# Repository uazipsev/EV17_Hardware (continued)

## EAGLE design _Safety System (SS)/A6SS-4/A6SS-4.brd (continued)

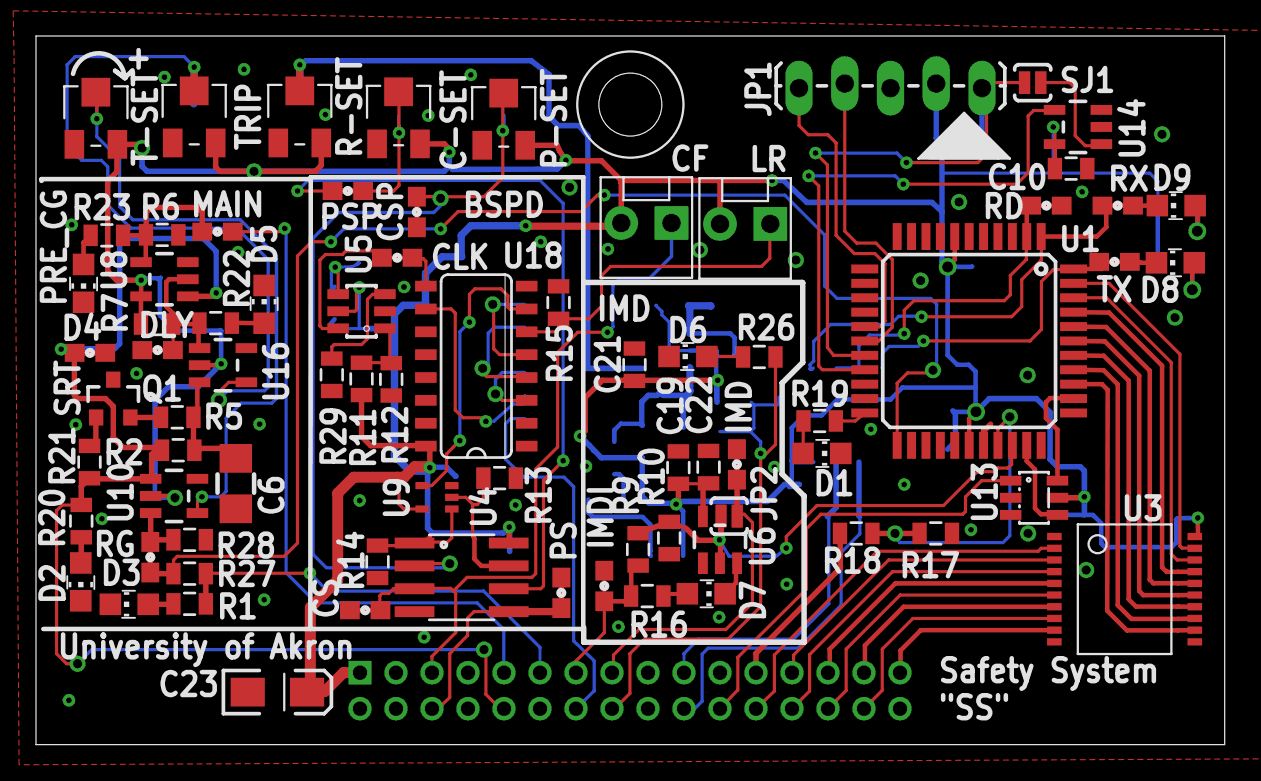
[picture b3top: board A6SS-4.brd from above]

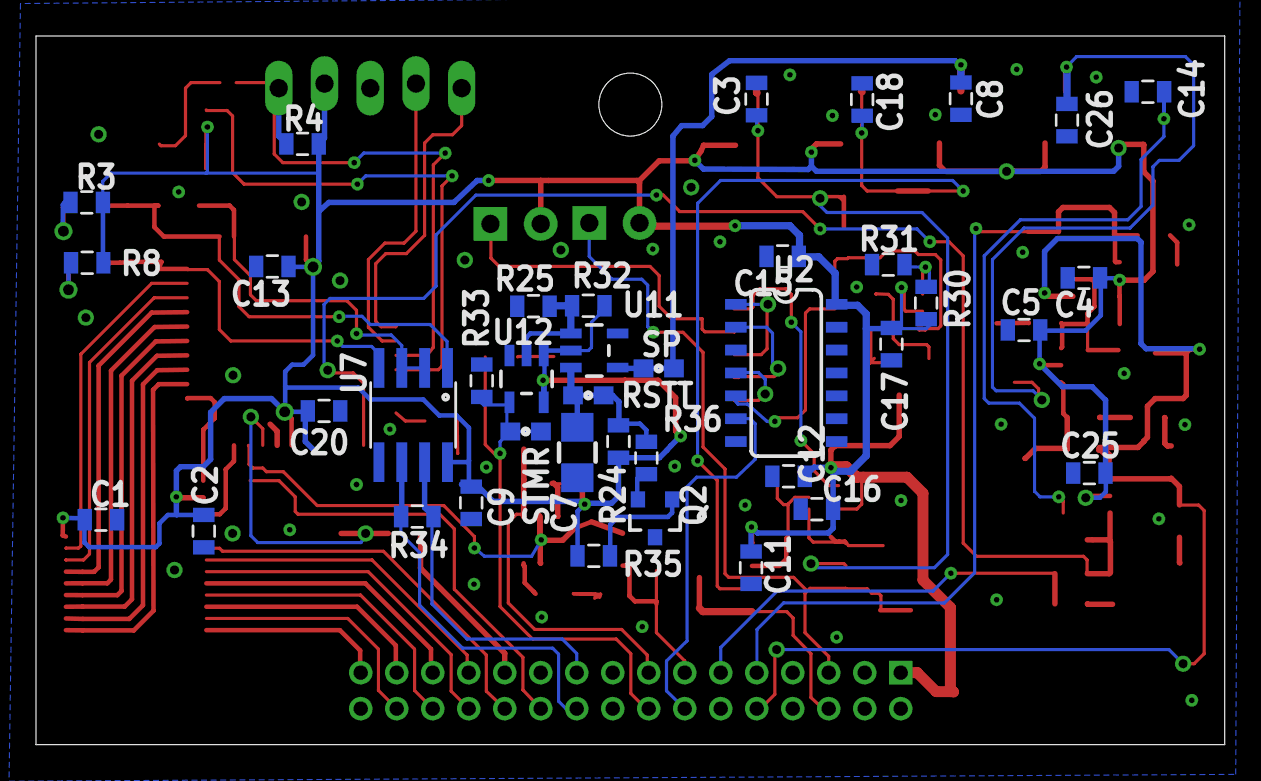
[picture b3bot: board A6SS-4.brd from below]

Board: 2 copper layers, 66.0 x 39.4 mm, 117 parts (39 on the bottom side), 79 nets.

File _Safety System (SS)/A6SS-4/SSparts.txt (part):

Partlist

Exported from A6SS-4.brd at 4/22/2016 5:32 PM

EAGLE Version 7.5.0 Copyright (c) 1988-2015 CadSoft

Assembly variant: 

Part     Value             Package            Library             Position (mil)        Orientation

C1       0.1UF             0805               FSAE Electric       (2457 491)            MR0
C2       0.1UF             0805               FSAE Electric       (2232 466)            MR270
C3       1UF               0805               FSAE Electric       (1023 1352)           MR270
C4       0.1UF             0805               FSAE Electric       (307 1020)            MR180
C5       0.1UF             0805               FSAE Electric       (438 906)             MR180
C6       100UF             1206               FSAE Electric       (436 570)             R270
C7       100UF             1206               FSAE Electric       (1342 689)            MR270
C8       1UF               0805               FSAE Electric       (576 1356)            MR270
C9       0.1UF             0805               FSAE Electric       (1671 530)            MR270
C10      0.1UF             0805               FSAE Electric       (2263 1259)           R0
C11      0.1UF             0805               FSAE Electric       (1035 386)            MR270
C12      0.1UF             0805               FSAE Electric       (891 514)             MR180
C13      0.1UF             0805               FSAE Electric       (2082 1045)           MR180
C14      1UF               0805               FSAE Electric       (167 1427)            MR180
C15      0.1UF             0805               FSAE Electric       (966 1067)            MR180
C16      0.1UF             0805               FSAE Electric       (953 586)             MR180
C17      0.1UF             0805               FSAE Electric       (728 875)             MR270
C18      1UF               0805               FSAE Electric       (794 1355)            MR270
C19      0.1UF             0805               FSAE Electric       (1404 605)            R90
C20      0.1UF             0805               FSAE Electric       (1969 729)            MR0
C21      0.1UF             0805               FSAE Electric       (1308 830)            R90
C22      0.1UF             0805               FSAE Electric       (1470 606)            R90
C23      10UF              EIA3216-16V        FSAE Electric       (527 114)             R0
C25      0.1UF             0805               FSAE Electric       (295 593)             MR180
C26      1UF               0805               FSAE Electric       (344 1365)            MR270
CARD1    CARD-2016CARD     CARD-2016          FSAE Electric       (-1 -1)               R0
CLK      TP                0603               FSAE Electric       (789 1064)            R0
CS       TP                0603               FSAE Electric       (719 293)             R180
CSP      TP                0603               FSAE Electric       (832 1164)            R90
D1       AMBER             CHIP_LED0805       FSAE Electric       (1718 636)            R270
D2       GREEN             CHIP_LED0805       FSAE Electric       (97 355)              R180
D3       GREEN             CHIP_LED0805       FSAE Electric       (203 306)             R90
D4       GREEN             CHIP_LED0805       FSAE Electric       (103 1008)            R180
D5       GREEN             CHIP_LED0805       FSAE Electric       (498 962)             R0
D6       GREEN             CHIP_LED0805       FSAE Electric       (1425 848)            R90
D7       GREEN             CHIP_LED0805       FSAE Electric       (1353 342)            R90
D8       GREEN             CHIP_LED0805       FSAE Electric       (2491 1053)           R90
D9       RED               CHIP_LED0805       FSAE Electric       (2493 1178)           R90
DLY      TP                0603               FSAE Electric       (265 862)             R0
IMD      TP                0603               FSAE Electric       (1532 612)            R270
IMDI     TP                0603               FSAE Electric       (1269 563)            R90
J1       M2M1X2            MOLEX-1X2          FSAE Electric       (1550 1138)           R180
J2       M2M1X2            MOLEX-1X2          FSAE Electric       (1334 1140)           R180
JP1                        1X05_LOCK_LONGPADS SparkFun-Connectors (2068 1435)           R180
JP2                        SJ_2S-NO           SparkFun-Passives   (1515 499)            R180
MAIN     TP                0603               FSAE Electric       (396 1121)            R180
POT1     22AR100KLFTR      22AR100KLFTR       FSAE Eletric        (130 1369)            R0
POT2     22AR100KLFTR      22AR100KLFTR       FSAE Eletric        (345 1372)            R0
POT3     22AR100KLFTR      22AR100KLFTR       FSAE Eletric        (792 1370)            R0
POT4     22AR100KLFTR      22AR100KLFTR       FSAE Eletric        (1022 1367)           R0
POT5     22AR100KLFTR      22AR100KLFTR       FSAE Eletric        (576 1372)            R0
PS       TP                0603               FSAE Electric       (1148 331)            R270
PSP      TP                0603               FSAE Electric       (681 1210)            R0
Q1       MMBT4403LT3G      SOT23              FSAE Electric       (168 754)             R0
R1       2.2K              0805               FSAE Electric       (335 307)             R0
R2       115K              0805               FSAE Electric       (310 643)             R0
R3       1K                0805               FSAE Electric       (2488 1185)           MR0
R4       10K               0805               FSAE Electric       (2016 1313)           MR0
R5       5                 0805               FSAE Electric       (308 715)             R0
R6       2.7K              0805               FSAE Electric       (275 1114)            R180
R7       2.7K              0805               FSAE Electric       (264 919)             R180
R8       1K                0805               FSAE Electric       (2487 1053)           MR0
R9       28K               0805               FSAE Electric       (1330 558)            R90
R10      5K                0805               FSAE Electric       (1330 437)            R90
R11      1k                0805               FSAE Electric       (711 799)             R270
R12      1k                0805               FSAE Electric       (776 798)             R90
R13      10K               0805               FSAE Electric       (960 524)             R270
R14      10K               0805               FSAE Electric       (746 399)             R90
R15      10K               0805               FSAE Electric       (1142 966)            R90
R16      1k                0805               FSAE Electric       (1395 437)            R90
R17      5K                0805               FSAE Electric       (1967 461)            R180
R18      28K               0805               FSAE Electric       (1793 461)            R180
R19      1K                0805               FSAE Electric       (1712 706)            R0
R20      1K                0805               FSAE Electric       (98 488)              R90
R21      1K                0805               FSAE Electric       (116 617)             R270
R22      1K                0805               FSAE Electric       (392 921)             R0
R23      1K                0805               FSAE Electric       (154 1113)            R180
R24      115K              0805               FSAE Electric       (1246 708)            MR90
R25      2.7K              0805               FSAE Electric       (1511 958)            MR0
R26      1K                0805               FSAE Electric       (1581 847)            R0
R27      28k               0805               FSAE Electric       (335 373)             R0
R28      5K                0805               FSAE Electric       (335 447)             R180
R29      91K               0805               FSAE Electric       (646 808)             R90
R30      976K              0805               FSAE Electric       (645 959)             MR270
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
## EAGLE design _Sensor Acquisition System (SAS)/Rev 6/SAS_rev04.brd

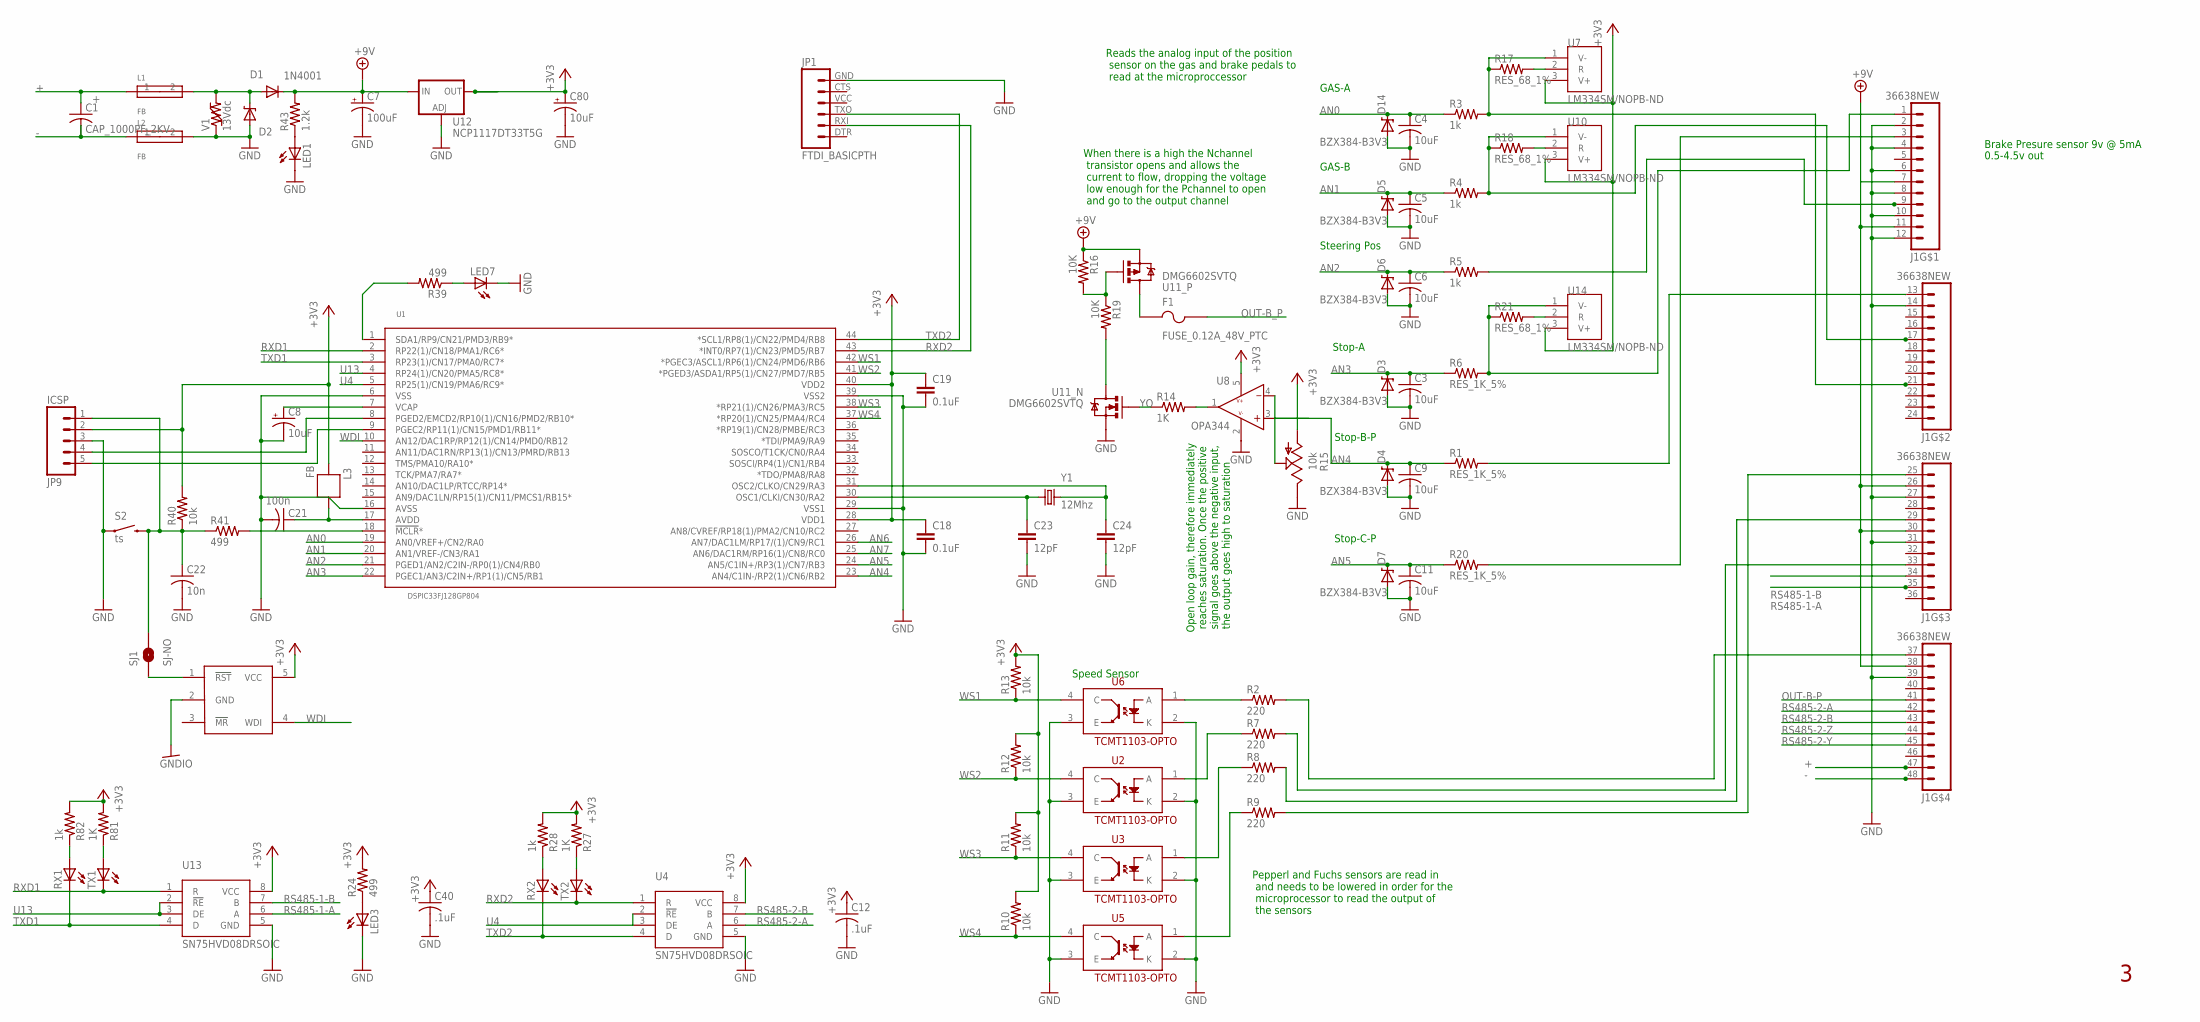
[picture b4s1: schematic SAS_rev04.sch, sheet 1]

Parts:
C1: CAP_1000PF_2KV; C1825
C3, C4, C5, C6, C9, C11: 10uF; C0805
C7: 100uF; EIA7343
C8: 10uF; EIA3216-16V
C12, C40: .1uF; 0603
C18, C19: 0.1uF; 0805
C21: 100n; C0805
C22: 10n; 0603
C23, C24: 12pF; 0805
C80: 10uF; POLC1206
D1: 1N4001; SOD123
D2: MM5Z30; SOD-523F
D3, D4, D5, D6, D7, D14: BZX384-B3V3; SOD-323
F1: FUSE_0.12A_48V_PTC; 1206
J1: 36638NEW; 36638-M
JP1: FTDI_BASICPTH; FTDI_BASIC
JP9: ICSP; 1X05_LOCK_LONGPADS
L1, L2, L3: FB; 0603
LED1, LED3, LED7: LEDCHIP-LED0805; CHIP-LED0805
R1, R6, R20: RES_1K_5%; 0603
R2, R7, R8, R9: 220; 0603
R3, R4, R5, R82: 1k; 0603
R10, R11, R12, R13: 10k; 0603
R14, R27: 1K; 0805
R15: 10k; PVG3
R16, R19: 10K; 0805
R17, R18, R21: RES_68_1%; 0603
R24, R39: 499; 0603
R28: 1k; 0805
R40: 10k; 0805
R41: 499; 0805
R43: 1.2k; 0805
R81: 1K; 0603
RX1, RX2: LEDCHIPLED_0805; CHIPLED_0805
S2: ts; TACTILE-PTH
SJ1: SJ-NO; SJ_2S-NO
TX1, TX2: LEDCHIPLED_0805; CHIPLED_0805
U1: DSPIC33FJ128GP804; TQFP-44
U2, U3, U5, U6: TCMT1103-OPTO; SSOP-4
U4, U13: SN75HVD08DRSOIC; SO-8
U7, U10, U14: LM334SM/NOPB-ND; SO-8
U8: OPA344; SOT23-5
U9: MAX823; SOT23-5L
U11: DMG6602SVTQ; SOT23-6
U12: NCP1117DT33T5G; V-REG_DPACK
V1: 13Vdc; 0603
Y1: 12Mhz; CRYSTAL-SMD-5X3

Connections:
+: C1.1 (+), J1.47 (11), L1.1
+3V3: C12.1 (+), C18.1, C19.1, C40.1 (+), C80.1 (+), JP9.2, L3.2, R10.2, R11.2, R12.2, R13.2, R15.1 (CW), R24.2, R27.2, R28.2, R40.2, R81.2, R82.2, U1.28 (VDD1), U1.40 (VDD2), U4.8 (VCC), U7.3 (V+), U8.5 (V+), U9.5 (VCC), U10.3 (V+), U12.4 (OUT), U13.8 (VCC), U14.3 (V+)
+9V: C7.A (+), D1.C, J1.7, J1.11, J1.26 (2), J1.30 (6), J1.38 (2), R16.1, R43.2, U11.2 (S), U12.3 (IN)
-: C1.2 (-), J1.48 (12), L2.1
AN0: C4.1, D14.1 (C), R3.1, U1.19 (AN0/VREF+/CN2/RA0)
AN1: C5.1, D5.1 (C), R4.1, U1.20 (AN1/VREF-/CN3/RA1)
AN2: C6.1, D6.1 (C), R5.1, U1.21 (PGED1/AN2/C2IN-/RP0(1)/CN4/RB0)
AN3: C3.1, D3.1 (C), R6.1, U1.22 (PGEC1/AN3/C2IN+/RP1(1)/CN5/RB1)
AN4: C9.1, D4.1 (C), R1.1, U1.23 (AN4/C1IN-/RP2(1)/CN6/RB2), U8.3 (+)
AN5: C11.1, D7.1 (C), R20.1, U1.24 (AN5/C1IN+/RP3(1)/CN7/RB3)
AN6: U1.26 (AN7/DAC1LM/RP17/(1)/CN9/RC1)
AN7: U1.25 (AN6/DAC1RM/RP16(1)/CN8/RC0)
GHT: D1.A, D2.C, L1.2, V1.2
GND: C3.2, C4.2, C5.2, C6.2, C7.C (-), C8.C (-), C9.2, C11.2, C12.2 (-), C18.2, C19.2, C21.2, C22.2 (-), C23.2, C24.2, C40.2 (-), C80.2 (-), D2.A, D3.2 (A), D4.2 (A), D5.2 (A), D6.2 (A), D7.2 (A), D14.2 (A), J1.2, J1.4, J1.6, J1.8, J1.10, J1.12, J1.14 (2), J1.27 (3), J1.31 (7), J1.39 (3), JP1.GND (6), JP9.3, L2.2, LED1.C, LED3.C, LED7.C, R15.3 (CCW), S2.1, U1.6 (VSS), U1.16 (AVSS), U1.29 (VSS1), U1.39 (VSS2), U2.2 (K), U2.3 (E), U3.2 (K), U3.3 (E), U4.5 (GND), U5.2 (K), U5.3 (E), U6.2 (K), U6.3 (E), U8.2 (V-), U11.5 (S), U12.1 (ADJ), U13.5 (GND), V1.1
GNDIO: U9.2 (GND)
unnamed: C22.1 (+), JP9.1, R40.1, R41.1, S2.3 (2), SJ1.2
unnamed: C21.1, L3.1, U1.17 (AVDD)
unnamed: J1.21 (9), R3.2, R17.1, U7.1 (V-)
unnamed: C8.A (+), U1.7 (VCAP)
unnamed: R39.2, U1.1 (SDA1/RP9/CN21/PMD3/RB9*)
unnamed: LED1.A, R43.1
unnamed: R17.2, U7.2 (R)
unnamed: R41.2, U1.18 (!MCLR!*)
unnamed: R15.2 (W), U8.4 (-)
unnamed: SJ1.1, U9.1 (!RST)
unnamed: J1.37 (1), R2.2
unnamed: JP9.4, U1.8 (PGED2/EMCD2/RP10(1)/CN16/PMD2/RB10*)
unnamed: JP9.5, U1.9 (PGEC2/RP11(1)/CN15/PMD1/RB11*)
unnamed: J1.33 (9), R7.2
unnamed: J1.29 (5), R8.2
unnamed: J1.25 (1), R9.2
unnamed: R2.1, U6.1 (A)
unnamed: R7.1, U2.1 (A)
unnamed: R8.1, U3.1 (A)
unnamed: R9.1, U5.1 (A)
unnamed: R18.2, U10.2 (R)
unnamed: LED3.A, R24.1
unnamed: J1.17 (5), R4.2, R18.1, U10.1 (V-)
unnamed: J1.9, R5.2
unnamed: R27.1, TX2.A
unnamed: R28.1, RX2.A
unnamed: R14.2, U8.1 (O)
unnamed: LED7.A, R39.1
unnamed: C24.1, U1.31 (OSC2/CLKO/CN29/RA3), Y1.3 (2)
unnamed: C23.1, U1.30 (OSC1/CLKI/CN30/RA2), Y1.1
unnamed: R19.2, U11.6 (D)
unnamed: R16.2, R19.1, U11.3 (G)
unnamed: F1.1, U11.4 (D)
unnamed: R21.2, U14.2 (R)
unnamed: R81.1, TX1.A
unnamed: R82.1, RX1.A
OUT-B-P: J1.41 (5)
OUT-B_P: F1.2
RS485-1-A: J1.35 (11), U13.6 (A)
RS485-1-B: J1.34 (10), U13.7 (B)
RS485-2-A: J1.42 (6), U4.6 (A)
RS485-2-B: J1.43 (7), U4.7 (B)
RS485-2-Y: J1.45 (9)
RS485-2-Z: J1.44 (8)
RXD1: TX1.C, U1.2 (RP22(1)/CN18/PMA1/RC6*), U13.1 (R)
RXD2: JP1.RXI (2), TX2.C, U1.43 (*INT0/RP7(1)/CN23/PMD5/RB7), U4.1 (R)
STOP-A: J1.1, R6.2, R21.1, U14.1 (V-)
STOP-B: J1.13 (1), R1.2
STOP-C: J1.3, R20.2
TXD1: RX1.C, U1.3 (RP23(1)/CN17/PMA0/RC7*), U13.4 (D)
TXD2: JP1.TXO (3), RX2.C, U1.44 (*SCL1/RP8(1)/CN22/PMD4/RB8), U4.4 (D)
U4: U1.5 (RP25(1)/CN19/PMA6/RC9*), U4.2 (!RE), U4.3 (DE)
U13: U1.4 (RP24(1)/CN20/PMA5/RC8*), U13.2 (!RE), U13.3 (DE)
WDI: U1.10 (AN12/DAC1RP/RP12(1)/CN14/PMD0/RB12), U9.4 (WDI)
WS1: R13.1, U1.42 (*PGEC3/ASCL1/RP6(1)/CN24/PMD6/RB6), U6.4 (C)
WS2: R12.1, U1.41 (*PGED3/ASDA1/RP5(1)/CN27/PMD7/RB5), U2.4 (C)
WS3: R11.1, U1.38 (*RP21(1)/CN26/PMA3/RC5), U3.4 (C)
WS4: R10.1, U1.37 (*RP20(1)/CN25/PMA4/RC4), U5.4 (C)
YO: R14.1, U11.1 (G)

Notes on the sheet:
GAS-A
GAS-B
Steering Pos
Stop-A
Stop-B-P
Stop-C-P
Speed Sensor
Brake Presure sensor 9v @ 5mA
0.5-4.5v out
Pepperl and Fuchs sensors are read in and needs to be lowered in order for the microprocessor to read the output of the sensors
Reads the analog input of the position sensor on the gas and brake pedals to read at the microproccessor
Open loop gain, therefore immediately reaches saturation. Once the positive signal goes above the negative input, the output goes high to saturation
When there is a high the Nchannel transistor opens and allows the current to flow, dropping the voltage low enough for the Pchannel to open and go to the output channel

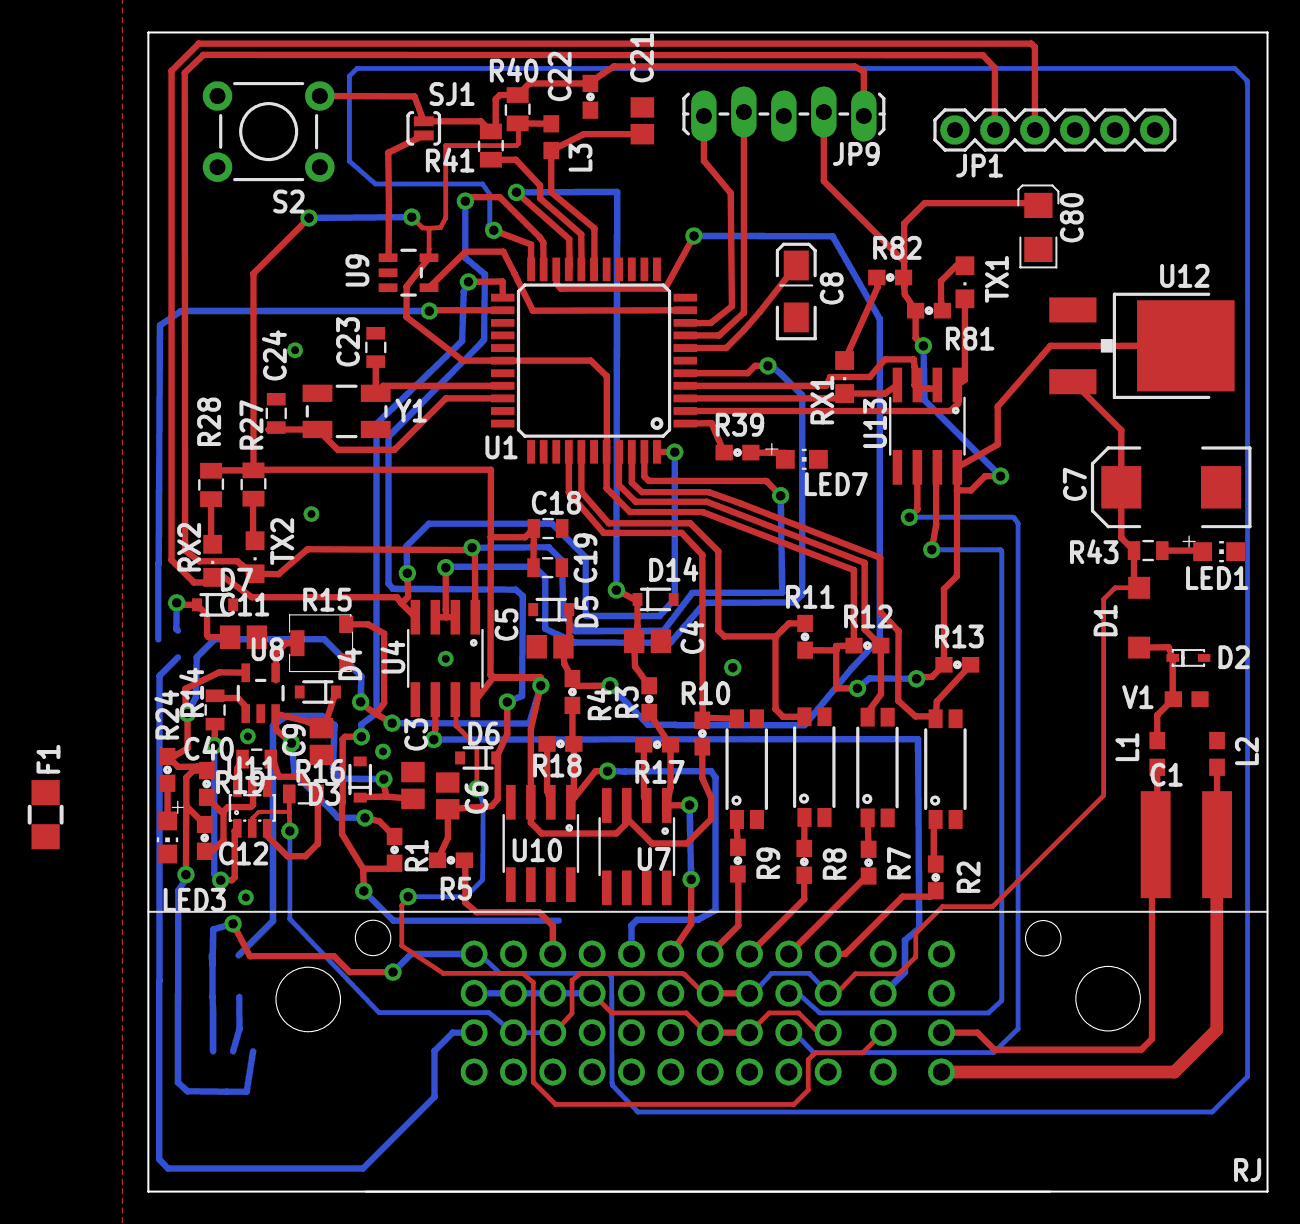
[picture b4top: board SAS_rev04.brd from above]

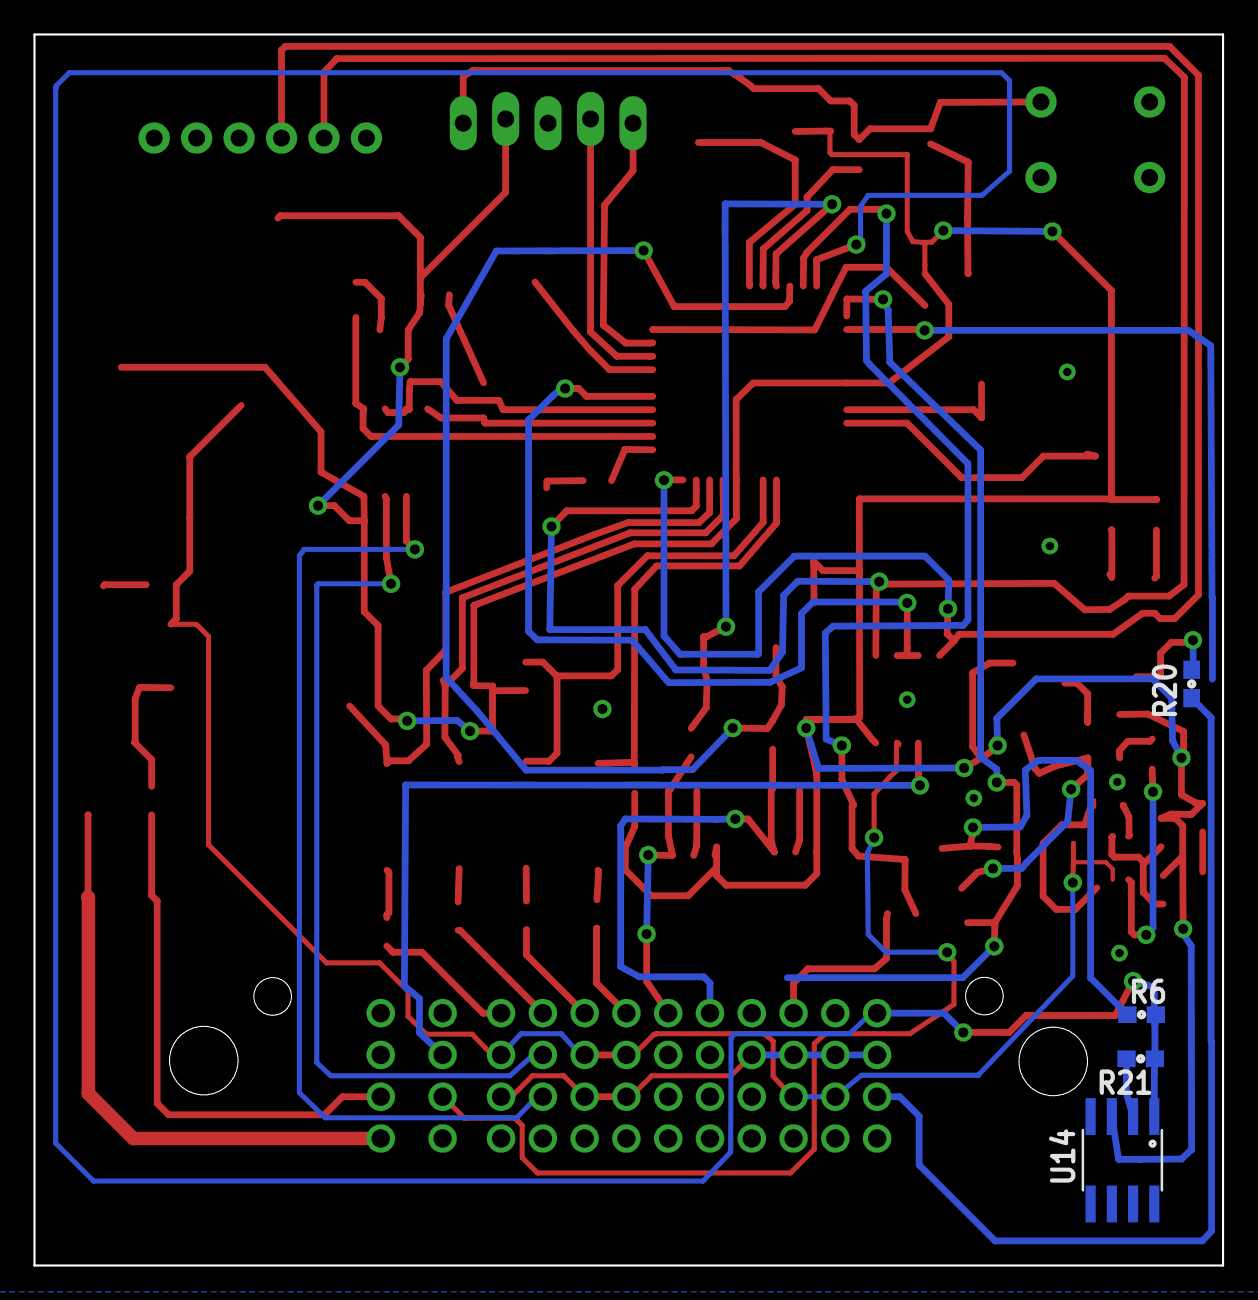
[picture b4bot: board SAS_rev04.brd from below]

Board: 2 copper layers, 71.1 x 73.7 mm, 88 parts (4 on the bottom side), 67 nets.

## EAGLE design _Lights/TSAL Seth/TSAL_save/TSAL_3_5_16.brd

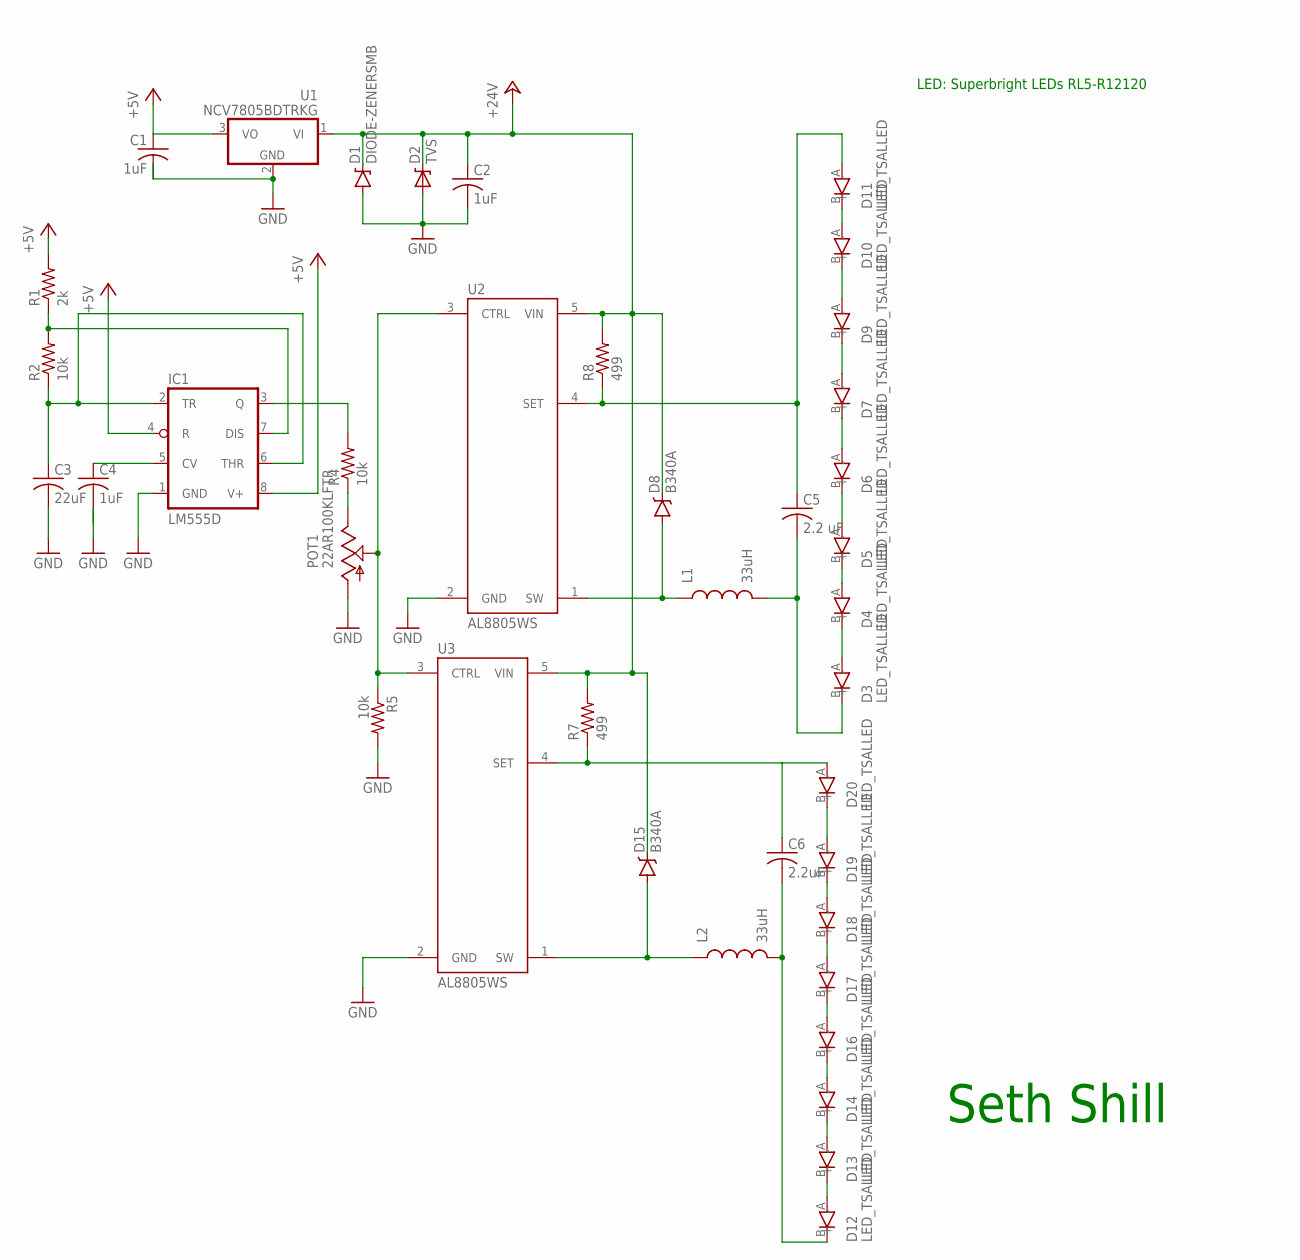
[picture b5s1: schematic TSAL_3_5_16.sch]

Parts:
C1, C2, C4: 1uF; 0805@1
C3: 22uF; 0805@1
C5: 2.2 uF; 0603@1
C6: 2.2uF; 0603@1
D1: DIODE-ZENERSMB; SMB-DIODE
D2: TVS; DO-214AC
D3, D4, D5, D6, D7, D9, D10, D11, D12, D13, D14, D16, D17, D18, D19, D20: LED_TSALLED; LED_TSAL
D8, D15: B340A; SMA-DIODE
IC1: LM555D; SO08
L1, L2: 33uH; 1007
POT1: 22AR100KLFTR
R1: 2k; 0805@1
R2, R4, R5: 10k; 0805@1
R7, R8: 499; 0603@1
U1: NCV7805BDTRKG; DPAK
U2, U3: AL8805WS; SOT23-5

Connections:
+5V: C1.1 (+), IC1.4 (R), IC1.8 (V+), R1.2, U1.3 (VO)
+24V: C2.1 (+), D1.C, D2.C, D8.C, D15.C, R7.2, R8.2, U1.1 (VI), U2.5 (VIN), U3.5 (VIN)
GND: C1.2 (-), C2.2 (-), C3.2 (-), C4.2 (-), D1.A, D2.A, IC1.1 (GND), POT1.3 (CW), R5.2, U1.2 (GND), U2.2 (GND), U3.2 (GND)
unnamed: C6.1 (+), D20.A (+), R7.1, U3.4 (SET)
unnamed: POT1.2 (W), R5.1, U2.3 (CTRL), U3.3 (CTRL)
unnamed: D17.A (+), D18.B (-)
unnamed: C4.1 (+), IC1.5 (CV)
unnamed: IC1.7 (DIS), R1.1, R2.2
unnamed: D15.A, L2.1, U3.1 (SW)
unnamed: C5.1 (+), D11.A (+), R8.1, U2.4 (SET)
unnamed: D10.A (+), D11.B (-)
unnamed: C3.1 (+), IC1.2 (TR), IC1.6 (THR), R2.1
unnamed: D18.A (+), D19.B (-)
unnamed: D9.A (+), D10.B (-)
unnamed: D7.A (+), D9.B (-)
unnamed: C6.2 (-), D12.B (-), L2.2
unnamed: D6.A (+), D7.B (-)
unnamed: D5.A (+), D6.B (-)
unnamed: D19.A (+), D20.B (-)
unnamed: D12.A (+), D13.B (-)
unnamed: C5.2 (-), D3.B (-), L1.2
unnamed: D13.A (+), D14.B (-)
unnamed: D16.A (+), D17.B (-)
unnamed: D14.A (+), D16.B (-)
unnamed: D4.A (+), D5.B (-)
unnamed: D3.A (+), D4.B (-)
unnamed: D8.A, L1.1, U2.1 (SW)
unnamed: POT1.1 (CCW), R4.1
unnamed: IC1.3 (Q), R4.2

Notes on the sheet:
LED: Superbright LEDs RL5-R12120
Seth Shill

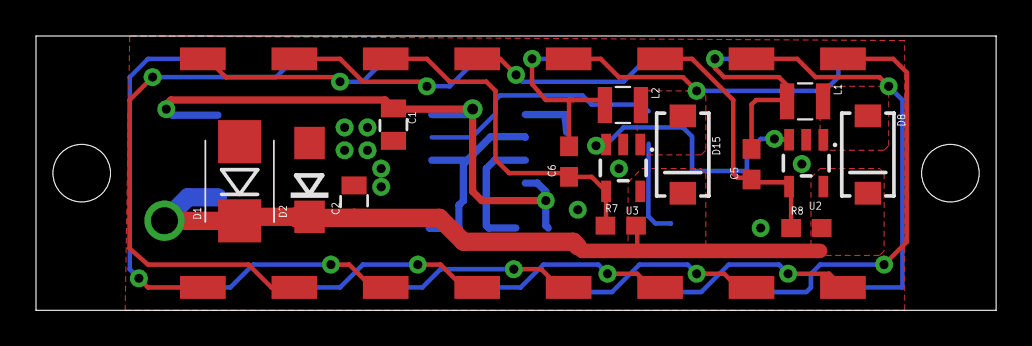
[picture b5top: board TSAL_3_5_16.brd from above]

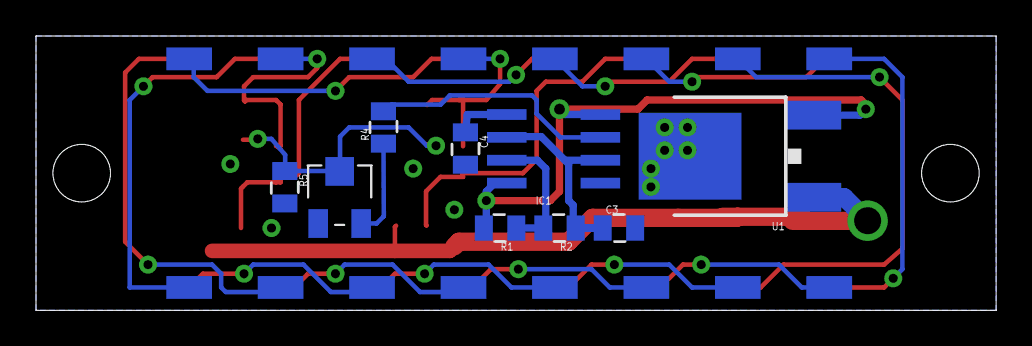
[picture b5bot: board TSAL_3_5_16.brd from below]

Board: 2 copper layers, 53.3 x 15.2 mm, 39 parts (9 on the bottom side), 29 nets.

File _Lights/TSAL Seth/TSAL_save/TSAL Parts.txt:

Partlist

Exported from TSAL_3_5_16.brd at 4/21/2016 5:39 PM

EAGLE Version 7.5.0 Copyright (c) 1988-2015 CadSoft

Assembly variant: 

Part     Value          Package      Library       Position (inch)       Orientation

C1       1uF            0805@1       FSAE Electric (0.78181102 0.40614961) R270
C2       1uF            0805@1       FSAE Electric (0.69568504 0.23773228) R90
C3       22uF           0805@1       FSAE Electric (0.825 0.18)          MR0
C4       1uF            0805@1       FSAE Electric (1.16074803 0.35380315) MR270
C5       2.2 uF         0603@1       FSAE Electric (1.56507874 0.31956693) R90
C6       2.2uF          0603@1       FSAE Electric (1.16594488 0.32531496) R90
D1       DIODE-ZENERSMB SMB-DIODE    FSAE Electric (0.4454252 0.28230709) R90
D2       TVS            DO-214AC     FSAE Electric (0.59837008 0.28530709) R90
D3       LED_TSALLED    LED_TSAL     FSAE Electric (1.565 0.55)          R0
D4       LED_TSALLED    LED_TSAL     FSAE Electric (1.765 0.05)          R0
D5       LED_TSALLED    LED_TSAL     FSAE Electric (1.365 0.05)          R0
D6       LED_TSALLED    LED_TSAL     FSAE Electric (0.965 0.05)          R0
D7       LED_TSALLED    LED_TSAL     FSAE Electric (0.565 0.05)          R0
D8       B340A          SMA-DIODE    FSAE Electric (1.81944882 0.34074803) R270
D9       LED_TSALLED    LED_TSAL     FSAE Electric (0.565 0.55)          R0
D10      LED_TSALLED    LED_TSAL     FSAE Electric (0.965 0.55)          R0
D11      LED_TSALLED    LED_TSAL     FSAE Electric (1.365 0.55)          R0
D12      LED_TSALLED    LED_TSAL     FSAE Electric (1.165 0.55)          R0
D13      LED_TSALLED    LED_TSAL     FSAE Electric (1.765 0.55)          R0
D14      LED_TSALLED    LED_TSAL     FSAE Electric (1.565 0.05)          R0
D15      B340A          SMA-DIODE    FSAE Electric (1.4146063 0.34062992) R270
D16      LED_TSALLED    LED_TSAL     FSAE Electric (1.165 0.05)          R0
D17      LED_TSALLED    LED_TSAL     FSAE Electric (0.765 0.05)          R0
D18      LED_TSALLED    LED_TSAL     FSAE Electric (0.365 0.05)          R0
D19      LED_TSALLED    LED_TSAL     FSAE Electric (0.365 0.55)          R180
D20      LED_TSALLED    LED_TSAL     FSAE Electric (0.765 0.55)          R0
IC1      LM555D         SO08         FSAE Electric (0.96795276 0.35325197) MR90
L1       33uH           1007         FSAE Electric (1.68220472 0.45704724) R270
L2       33uH           1007         FSAE Electric (1.28370079 0.44909449) R270
POT1     22AR100KLFTR   22AR100KLFTR FSAE Electric (1.43580315 0.24681102) MR0
R1       2k             0805@1       FSAE Electric (1.085 0.18)          MR180
R2       10k            0805@1       FSAE Electric (0.955 0.18)          MR180
R4       10k            0805@1       FSAE Electric (1.34 0.4)            MR90
R5       10k            0805@1       FSAE Electric (1.55582677 0.26927559) MR270
R7       499            0603@1       FSAE Electric (1.27897638 0.18519685) R0
R8       499            0603@1       FSAE Electric (1.68511811 0.18007874) R0
U1       NCV7805BDTRKG  DPAK         FSAE Electric (0.55689764 0.33707087) MR90
U2       AL8805WS       SOT23-5      FSAE Electric (1.68464567 0.32185039) R180
U3       AL8805WS       SOT23-5      FSAE Electric (1.28429134 0.31141732) R180

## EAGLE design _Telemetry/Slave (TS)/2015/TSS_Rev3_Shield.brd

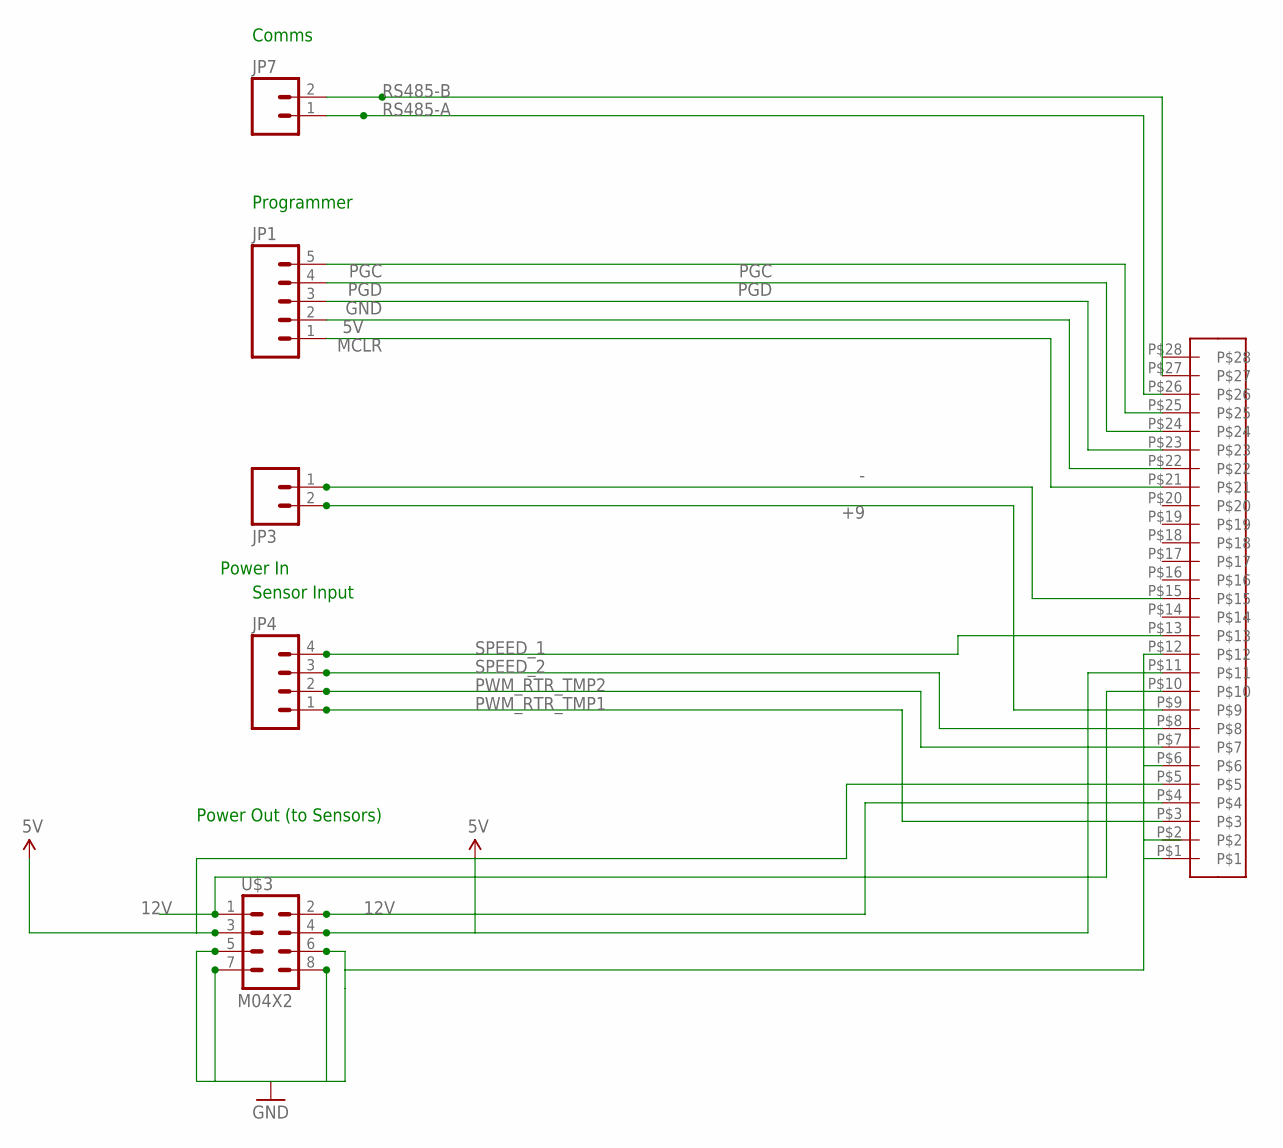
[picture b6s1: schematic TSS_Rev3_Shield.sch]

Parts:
JP1: M05PTH; 1X05
JP3: M02LOCK; 1X02_LOCK
JP4: M04PTH; 1X04
JP7: M02PTH; 1X02
U$1: 1-207216-6
U$3: M04X2; 2X4

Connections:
5V: JP1.2, U$1.P$5, U$1.P$11, U$1.P$22, U$3.3, U$3.4
12V: U$1.P$4, U$1.P$10, U$3.1, U$3.2
+9: JP3.2, U$1.P$9
-: JP3.1, U$1.P$15
GND: JP1.3, U$1.P$1, U$1.P$6, U$1.P$12, U$1.P$23, U$3.5, U$3.6, U$3.7, U$3.8
MCLR: JP1.1, U$1.P$21
PGC: JP1.5, U$1.P$25
PGD: JP1.4, U$1.P$24
PWM_RTR_TMP1: JP4.1, U$1.P$3
PWM_RTR_TMP2: JP4.2, U$1.P$7
RS485-A: JP7.1, U$1.P$26
RS485-B: JP7.2, U$1.P$27
SPEED_1: JP4.4, U$1.P$13
SPEED_2: JP4.3, U$1.P$8

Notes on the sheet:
Power In
Comms
Sensor Input
Programmer
Power Out (to Sensors)
